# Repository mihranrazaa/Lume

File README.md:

# Lume

An Open Source alternative of Kindle which gives you freedom to download and read anything you want.

----

## Overview 

Lume is a open source eBook Reader made for people who value freedom, simplicity and are fed up by the limitations and companies not valuing ownership . With Lume, you're free to choose how you read and what you install.

---

## Specifications
### Features(V0.1)

- Simple Menu System
- Bookmark System
- Joystick for smooth navigation
- Reading files ofc
- Offline-First
- approx1 week battery life (on medium usage)

### Hardware Support

- 7.5inch E-ink display
- Raspberry PI Zero 2w
- 5 way joystick navigation
- 4 Push buttons

### Controls

- **Joystick : Navigate menu items
- **Joystick : Turn pages while reading
- **Joystick : Select item
- **Button 1 : Return to menu
- **Button 2 : Back/Return to menu
- **Button 3 : Bookmark current page
- **Button 4 : Settings

---
## Files to Build

### PCB

The files for the PCB and Schematics are available in the PCB folder and gerber files are added in the Production folder..

### 3D Case(CAD)

The step files for the keyboard are available in the CAD folder and also in the Production Folder.

**BASE**

**PLATE**

---
## Images

---
## BOM

| Components            | Quantity | Price       | Link                                                                                                                                                                                      |
| --------------------- | -------- | ----------- | ----------------------------------------------------------------------------------------------------------------------------------------------------------------------------------------- |
| Raspberry pi zero 2w  | 1        | 16USD       | [Available](https://www.fabtolab.com/raspberry-pi-zero-2-w-rp3a0-1ghz-quad-core-64-bit-arm-cortex-a53-cpu-512mb-sdram-wireless-lan-mini-hdmi-port-micro-usb?search=Raspberry%20pi%20zero) |
| 7.5inch E-ink Display | 1        | 63USD       | [Available](https://hubtronics.in/7-5-inch-e-paper-hat?search=7.5%20inch%20e%20ink%20)                                                                                                    |
| 5D Joystick           | 1        | 0.58USD     | [Available](https://hubtronics.in/5d-rocker-joystick?search=joystick)                                                                                                                     |
| Tactile push buttons  | 4        | 0.28USD     |                                                                                                                                                                                           |
| PCB                   |          | approx10USD |                                                                                                                                                                                           |
| UPS                   | 1        | 27USD       | [Available](https://hubtronics.in/ups-hat-c?search=ups%20hat%20)                                                                                                                          |
* Forgot to add an SD Card in there my bad

**Total ::  110-130USD**

---
## Next Update

- Add more support for different file types
- More Reading features
- Ability to transfer files via Wifi or Bluetooth 
- Progress bar

---
## Extra Stuff

### Gratitude
- Thanks to Hackclub for making me do this brilliant project, More coming :).
- Thanks to my potato for helping me till the end.
- Thanks to myself for completing the project and not getting distracted with another project.
- And Thank you for Reading?

### Inspiration
I always wanted a ebook reader and i was thinking of buying kindle but then got to know it's limitations so why not build my own :).

### Challanging
Building the custom case.. i don't have the words to express my pain...

---

## End
Check my [BLOG](https://mihranrazaa.pages.dev/)
~ mihranrazaa

BYEEE

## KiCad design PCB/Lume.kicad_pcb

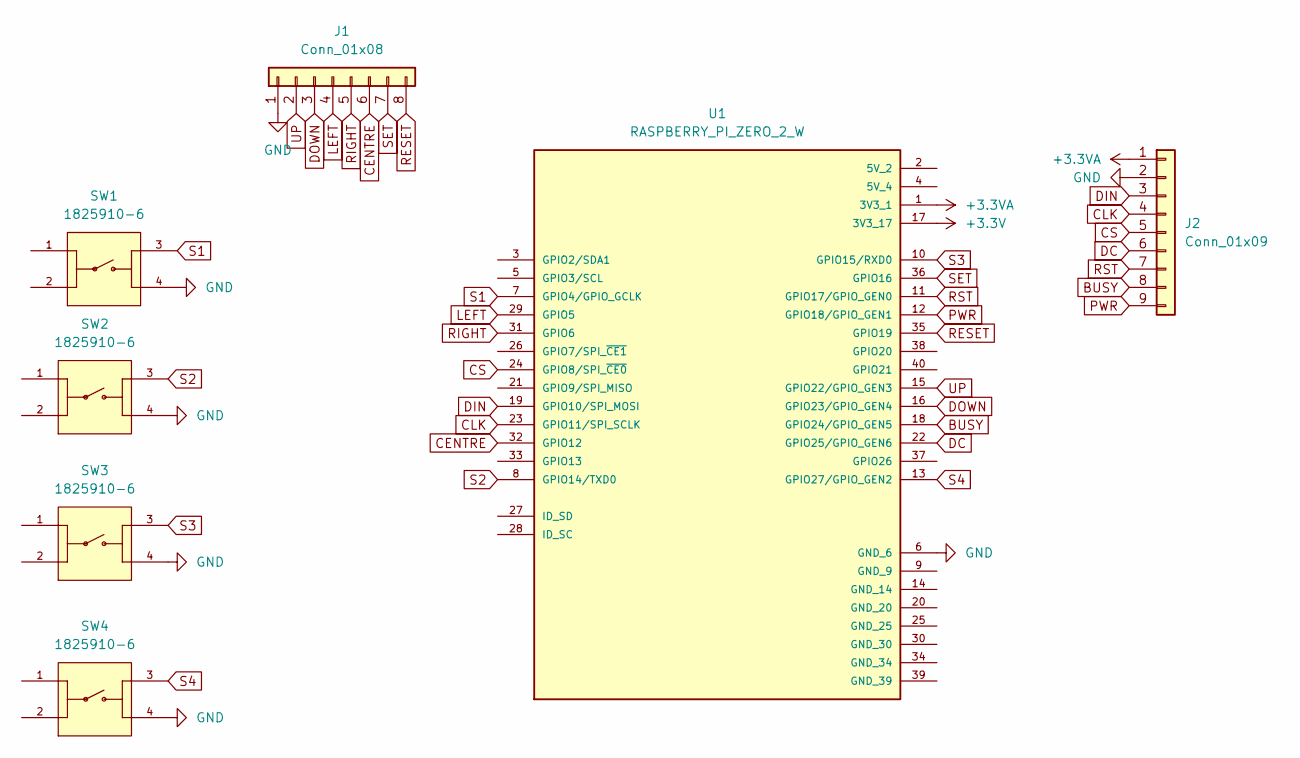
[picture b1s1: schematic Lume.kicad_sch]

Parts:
J1: Conn_01x08; PinHeader_1x08_P2.54mm_Horizontal
J2: Conn_01x09; PinHeader_1x09_P2.54mm_Horizontal
SW1, SW2, SW3, SW4: 1825910-6; SW_1825910-6-43D; PARTREV C10
U1: RASPBERRY_PI_ZERO_2_W; MODULE_RASPBERRY_PI_ZERO_2_W; PARTREV April 2024

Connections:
+3.3V: U1.17 (3V3_17)
+3.3VA: J2.1, U1.1 (3V3_1)
BUSY: J2.8, U1.18 (GPIO24/GPIO_GEN5)
CENTRE: J1.6, U1.32 (GPIO12)
CLK: J2.4, U1.23 (GPIO11/SPI_SCLK)
CS: J2.5, U1.24 (GPIO8/SPI_~CE0)
DC: J2.6, U1.22 (GPIO25/GPIO_GEN6)
DIN: J2.3, U1.19 (GPIO10/SPI_MOSI)
DOWN: J1.3, U1.16 (GPIO23/GPIO_GEN4)
GND: J1.1, J2.2, SW1.4, SW2.4, SW3.4, SW4.4, U1.6 (GND_6)
LEFT: J1.4, U1.29 (GPIO5)
PWR: J2.9, U1.12 (GPIO18/GPIO_GEN1)
RESET: J1.8, U1.35 (GPIO19)
RIGHT: J1.5, U1.31 (GPIO6)
RST: J2.7, U1.11 (GPIO17/GPIO_GEN0)
S1: SW1.3, U1.7 (GPIO4/GPIO_GCLK)
S2: SW2.3, U1.8 (GPIO14/TXD0)
S3: SW3.3, U1.10 (GPIO15/RXD0)
S4: SW4.3, U1.13 (GPIO27/GPIO_GEN2)
SET: J1.7, U1.36 (GPIO16)
UP: J1.2, U1.15 (GPIO22/GPIO_GEN3)

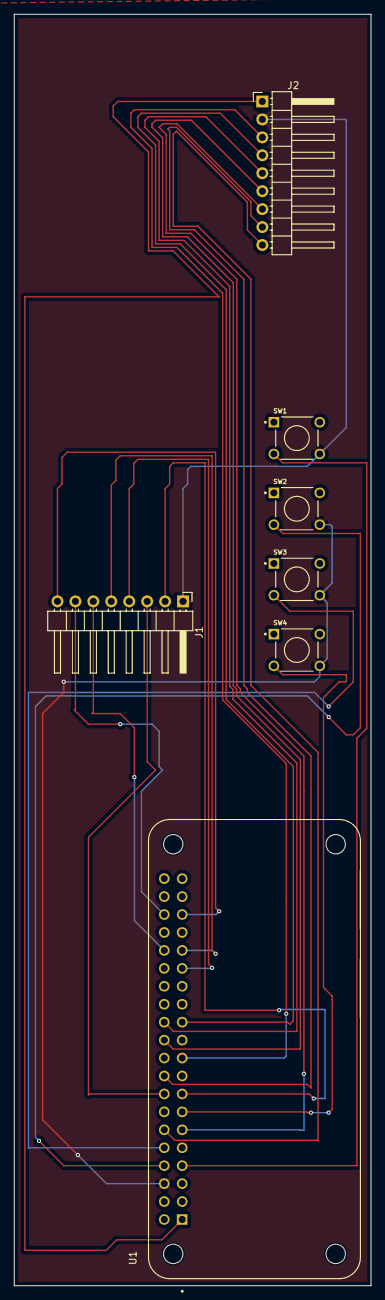
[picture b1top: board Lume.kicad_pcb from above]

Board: 2 copper layers, 50.5 x 180.0 mm, 7 parts (0 on the bottom side), 20 nets.

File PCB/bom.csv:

Designator,Footprint,Quantity,Value,LCSC Part #
J1,PinHeader_1x08_P2.54mm_Horizontal,1,Conn_01x08,
J2,PinHeader_1x09_P2.54mm_Horizontal,1,Conn_01x09,
"SW1, SW2, SW3, SW4",SW_1825910-6-43D,4,1825910-6,
U1,MODULE_RASPBERRY_PI_ZERO_2_W,1,RASPBERRY_PI_ZERO_2_W,

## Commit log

2025-07-14 Add Journal.md
2025-07-16 update v1
2025-07-18 add more file type support
2025-07-18 update firmware
